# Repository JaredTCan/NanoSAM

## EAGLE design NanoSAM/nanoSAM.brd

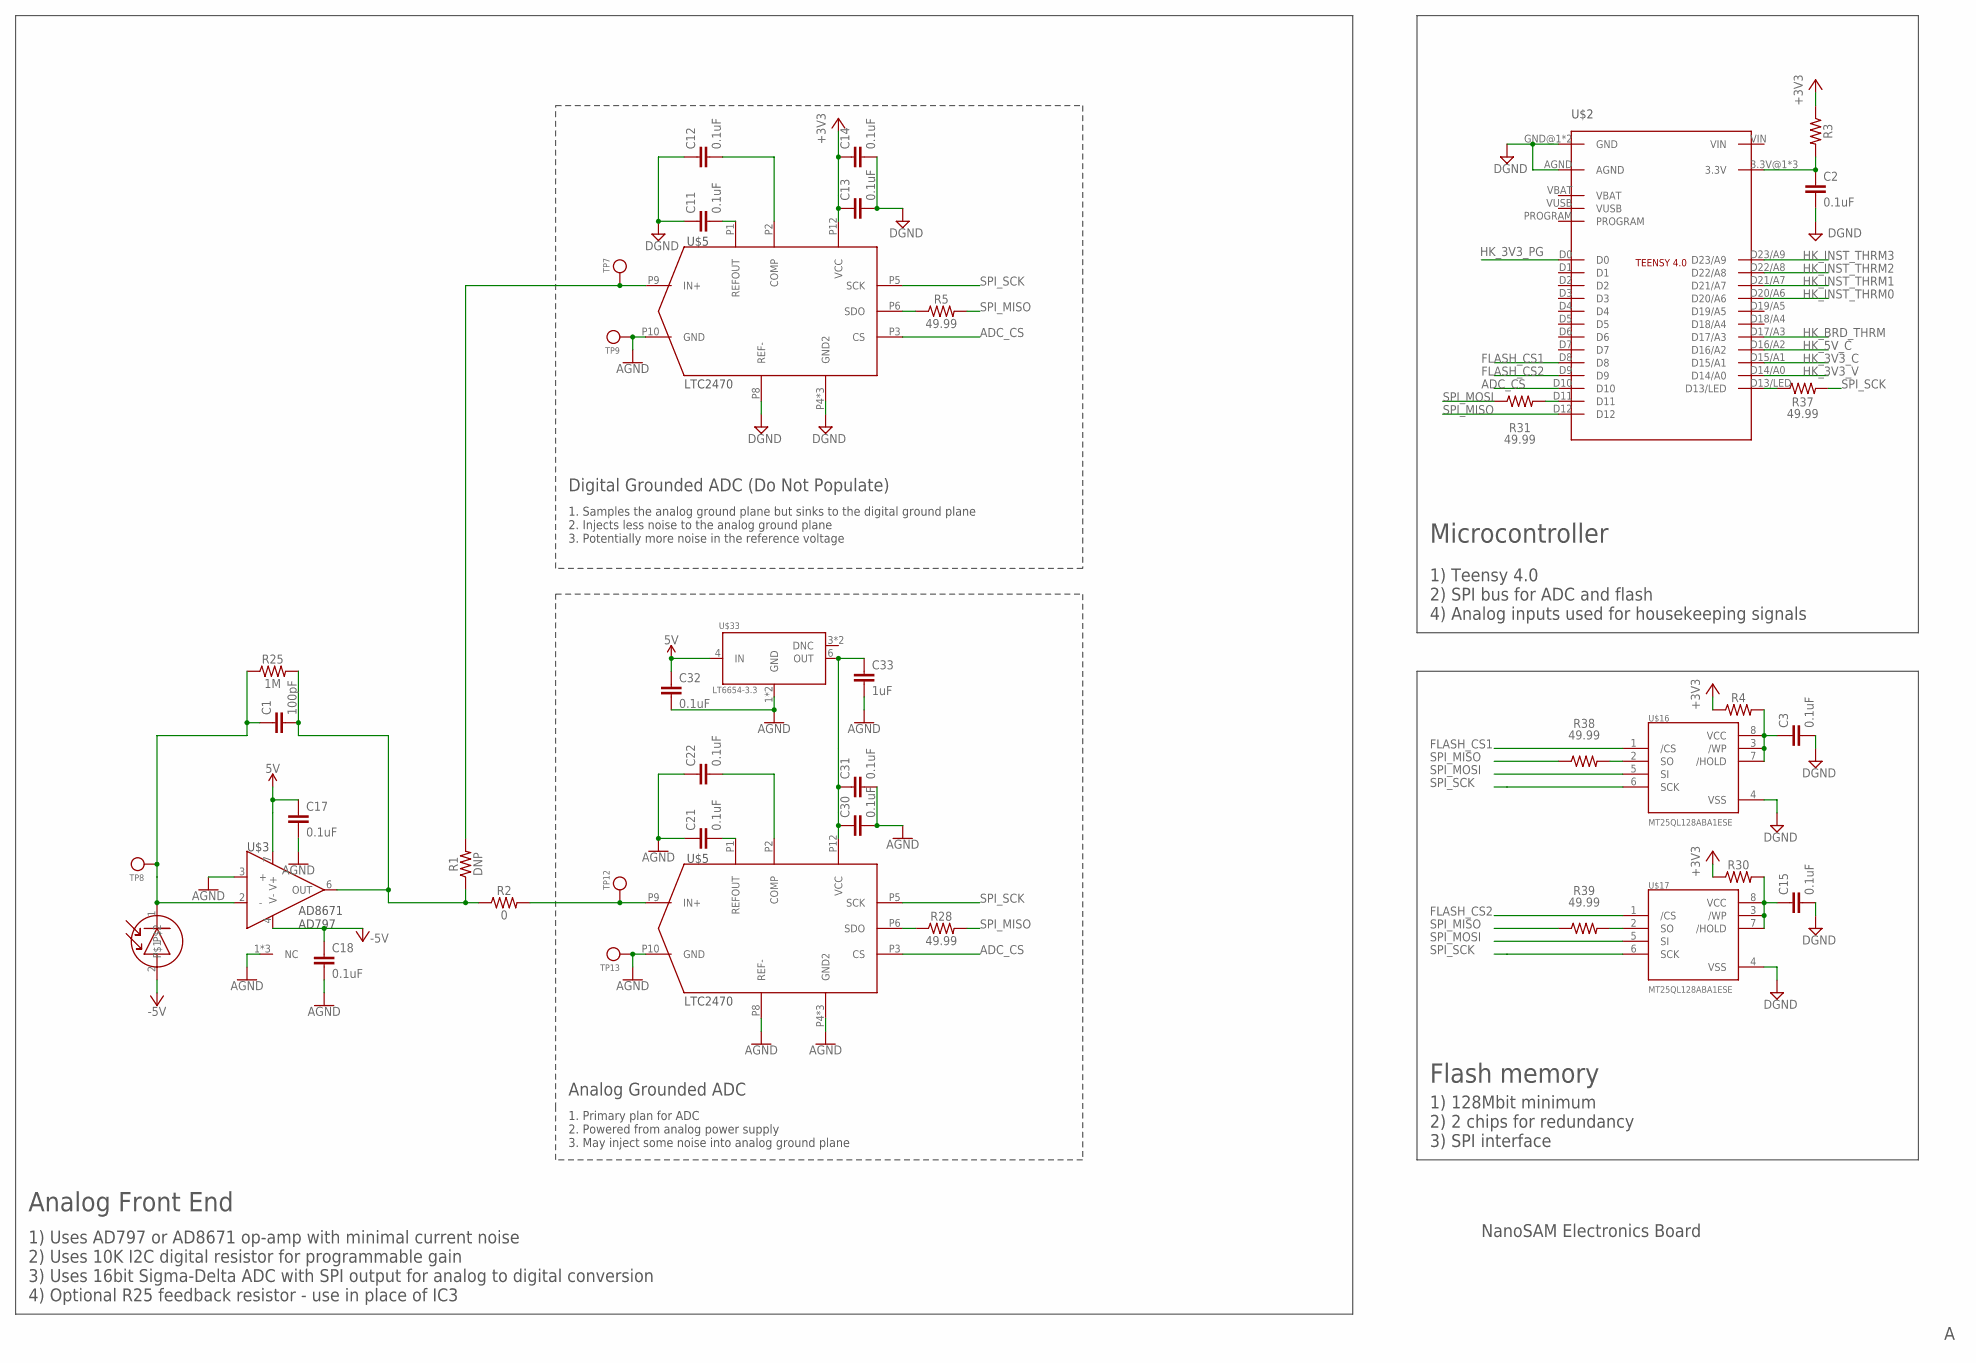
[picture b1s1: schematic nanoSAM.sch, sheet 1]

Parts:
C1: 100pF; 0603
C2, C3, C11, C12, C13, C14, C15, C17, C18, C21, C22, C30, C31, C32: 0.1uF; 0603
C33: 1uF; 0603
R1: DNP; 0805
R2: 0; 0805
R3, R4, R30: 0805
R5, R28, R31, R37, R38, R39: 49.99; 0805
R25: 1M; 0805
TP7, TP8, TP9, TP12, TP13: TESTPOINT; 1X01
U$1: PHOTODIODESYMBOLPD_CONN; 1X02
U$2: TEENSY4.0
U$3: AD8671; SO8
U$5, U$26: LTC2470; MSOP12
U$16, U$17: MT25QL128ABA1ESE; SO-08M
U$33: LT6654-3.3; SOT23-6L

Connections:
5V: C17.1, C32.1, U$3.7 (V+), U$33.4 (IN); also elsewhere on the board
+3V3: C13.1, C14.1, R3.1, R4.1, R30.1, U$5.P12 (VCC); also elsewhere on the board
-5V: C18.1, U$1.2, U$3.4 (V-); also elsewhere on the board
ADC_CS: U$2.D10, U$5.P3 (CS), U$26.P3 (CS)
AGND: C17.2, C18.2, C21.1, C22.1, C30.2, C31.2, C32.2, C33.2, TP9.1, TP13.1, U$3.1 (NC), U$3.3 (+), U$3.5 (NC), U$3.8 (NC), U$5.P10 (GND), U$26.P4 (GND2), U$26.P7 (GND2), U$26.P8 (REF-), U$26.P10 (GND), U$26.P11 (GND2), U$33.1 (GND), U$33.2 (GND); also elsewhere on the board
DGND: C2.2, C3.2, C11.1, C12.1, C13.2, C14.2, C15.2, U$2.AGND, U$2.GND@1 (GND), U$2.GND@2 (GND), U$5.P4 (GND2), U$5.P7 (GND2), U$5.P8 (REF-), U$5.P11 (GND2), U$16.4 (VSS), U$17.4 (VSS); also elsewhere on the board
FLASH_CS1: U$2.D8, U$16.1 (/CS)
FLASH_CS2: U$2.D9, U$17.1 (/CS)
HK_3V3_C: U$2.D15/A1; also elsewhere on the board
HK_3V3_PG: U$2.D0; also elsewhere on the board
HK_3V3_V: U$2.D14/A0; also elsewhere on the board
HK_5V_C: U$2.D16/A2; also elsewhere on the board
HK_BRD_THRM: U$2.D17/A3; also elsewhere on the board
HK_INST_THRM0: U$2.D20/A6; also elsewhere on the board
HK_INST_THRM1: U$2.D21/A7; also elsewhere on the board
HK_INST_THRM2: U$2.D22/A8; also elsewhere on the board
HK_INST_THRM3: U$2.D23/A9; also elsewhere on the board
unnamed: C1.1, R25.1, TP8.1, U$1.1, U$3.2 (-)
unnamed: C1.2, R1.1, R2.1, R25.2, U$3.6 (OUT)
unnamed: R1.2, TP7.1, U$5.P9 (IN+)
unnamed: C2.1, R3.2, U$2.3.3V@1 (3.3V), U$2.3.3V@2 (3.3V), U$2.ON/OFF (3.3V)
unnamed: R2.2, TP12.1, U$26.P9 (IN+)
unnamed: C3.1, R4.2, U$16.3 (/WP), U$16.7 (/HOLD), U$16.8 (VCC)
unnamed: C22.2, U$26.P2 (COMP)
unnamed: C12.2, U$5.P2 (COMP)
unnamed: C11.2, U$5.P1 (REFOUT)
unnamed: C21.2, U$26.P1 (REFOUT)
unnamed: C30.1, C31.1, C33.1, U$26.P12 (VCC), U$33.6 (OUT)
unnamed: C15.1, R30.2, U$17.3 (/WP), U$17.7 (/HOLD), U$17.8 (VCC)
unnamed: R5.1, U$5.P6 (SDO)
unnamed: R28.1, U$26.P6 (SDO)
unnamed: R31.2, U$2.D11
unnamed: R37.1, U$2.D13/LED
unnamed: R38.2, U$16.2 (SO)
unnamed: R39.2, U$17.2 (SO)
SPI_MISO: R5.2, R28.2, R38.1, R39.1, U$2.D12
SPI_MOSI: R31.1, U$16.5 (SI), U$17.5 (SI)
SPI_SCK: R37.2, U$5.P5 (SCK), U$16.6 (SCK), U$17.6 (SCK), U$26.P5 (SCK)

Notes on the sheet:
Analog Front End
Microcontroller
Flash memory
1) Uses AD797 or AD8671 op-amp with minimal current noise 2) Uses 10K I2C digital resistor for programmable gain 3) Uses 16bit Sigma-Delta ADC with SPI output for analog to digital conversion 4) Optional R25 feedback resistor - use in place of IC3
1) Teensy 4.0 2) SPI bus for ADC and flash 4) Analog inputs used for housekeeping signals
1) 128Mbit minimum 2) 2 chips for redundancy 3) SPI interface
AD8671 AD797
U$3
U$2
LTC2470
U$5
NanoSAM Electronics Board
Analog Grounded ADC
1. Primary plan for ADC 2. Powered from analog power supply 3. May inject some noise into analog ground plane
Digital Grounded ADC (Do Not Populate)
1. Samples the analog ground plane but sinks to the digital ground plane 2. Injects less noise to the analog ground plane 3. Potentially more noise in the reference voltage

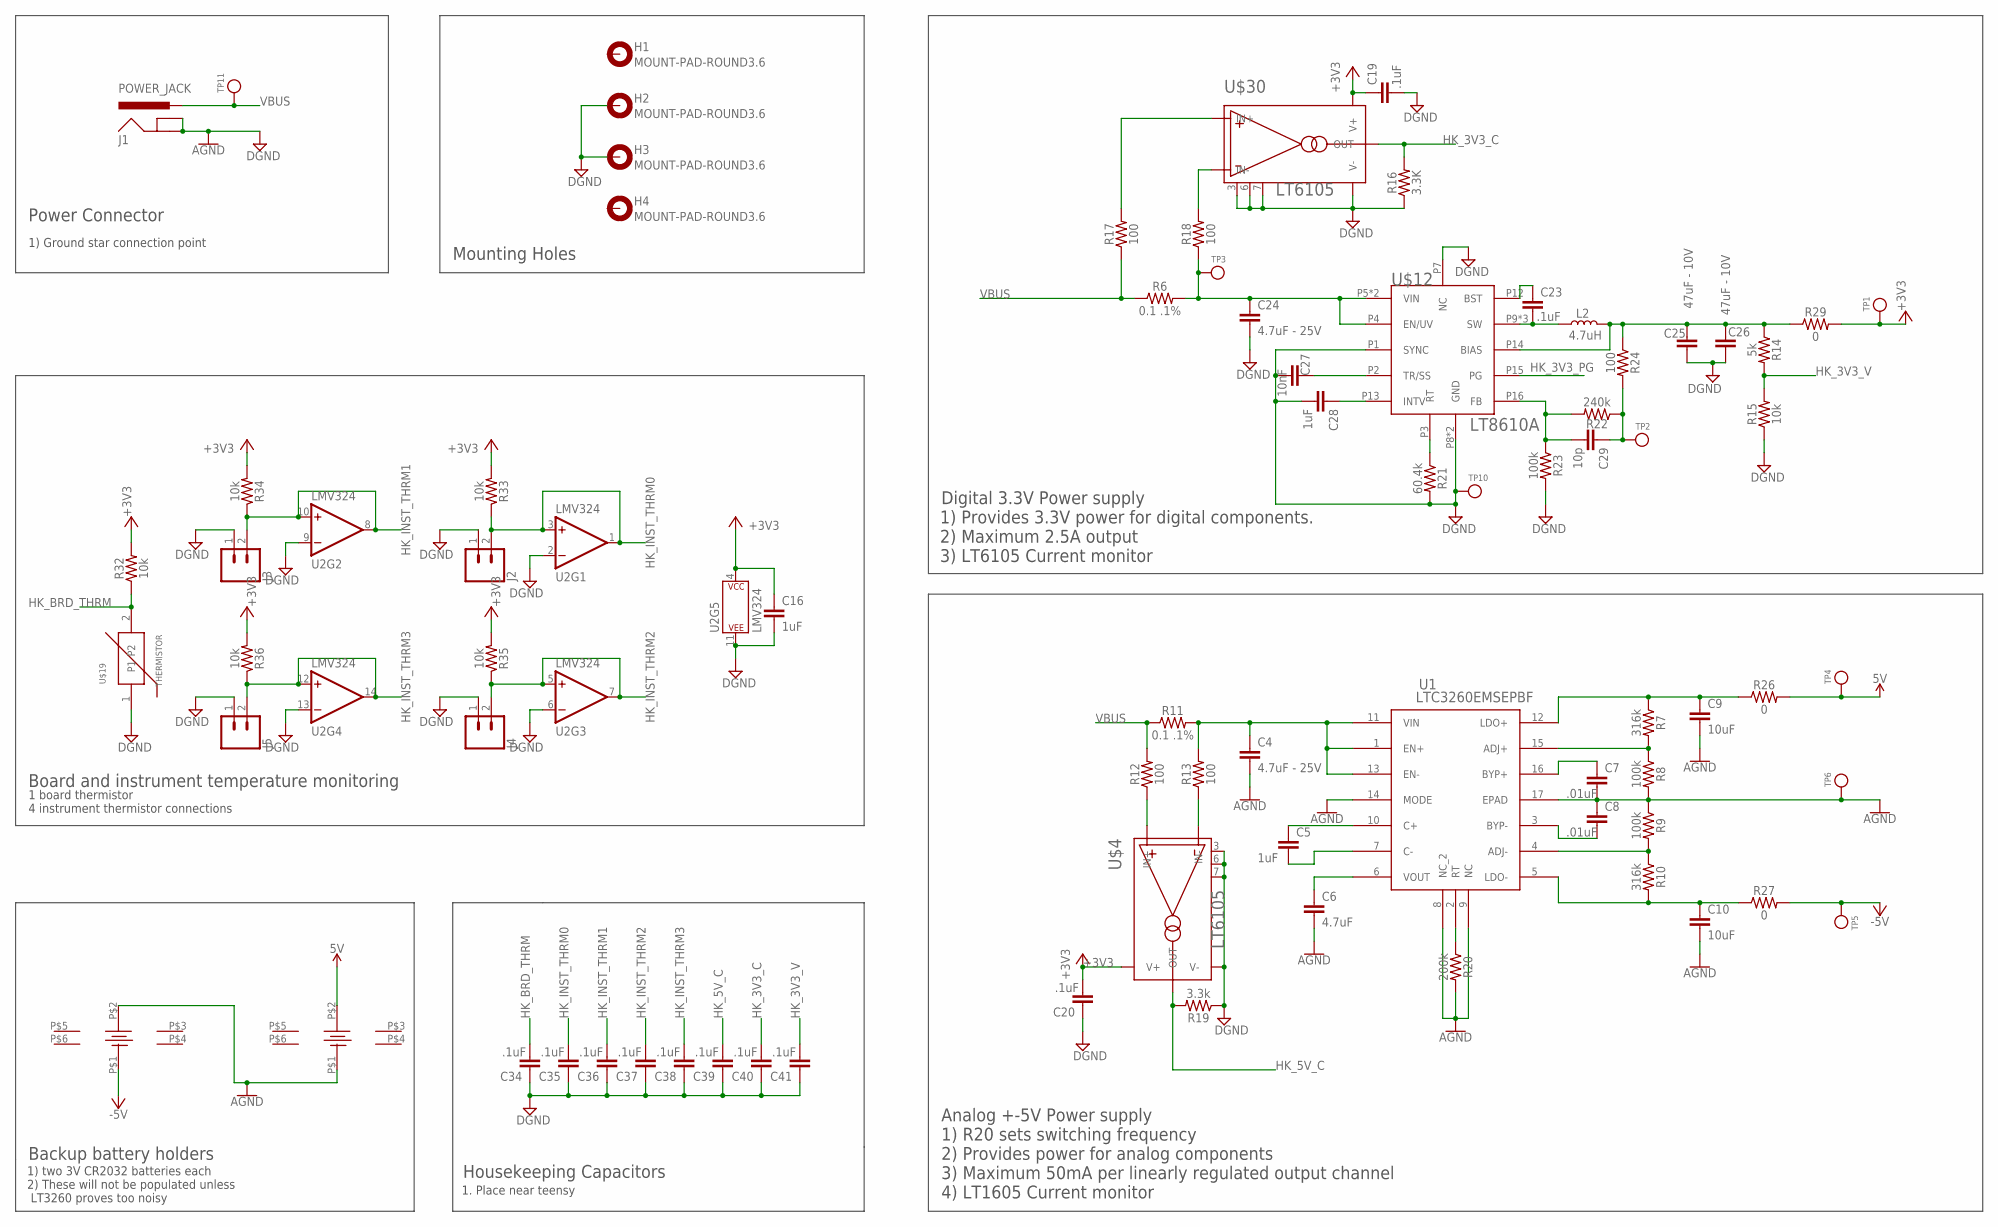
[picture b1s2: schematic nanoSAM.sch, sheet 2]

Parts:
C4, C24: 4.7uF - 25V; 1206
C5: 1uF; 1206
C6: 4.7uF; 1206
C7, C8: .01uF; 1206
C9, C10: 10uF; 1206
C16, C28: 1uF; 0603
C19, C20, C23, C34, C35, C36, C37, C38, C39, C40, C41: .1uF; 0603
C25, C26: 47uF - 10V; 1210
C27: 10nF; 0603
C29: 10p; 0603
H1, H2, H3, H4: MOUNT-PAD-ROUND3.6; 3,6-PAD
J1: POWER_JACK; POWER_JACK_PTH
J2, J3, J4, J5: CONN_02; 1X02
L2: 4.7uH; WE-HCI
R6, R11: 0.1 .1%; 1206
R7, R10: 316k; 0603
R8, R9, R23: 100k; 0603
R12, R13, R17, R18, R24: 100; 0603
R14: 5k; 0603
R15: 10k; 0603
R16: 3.3K; 0603
R19: 3.3k; 0603
R20: 200k; 0603
R21: 60.4k; 0603
R22: 240k; 0603
R26, R27: 0; 0603
R29: 0; 1206
R32, R33, R34, R35, R36: 10k; 1206
TP1, TP2, TP3, TP4, TP5, TP6, TP10, TP11: TESTPOINT; 1X01
U1: LTC3260EMSEPBF; MSOP-16_MSE
U2: LMV324; SO14
U$4, U$30: LT6105; MSOP8
U$12: LT8610A; MSOP16
U$19: THERMISTOR; M0805
U$20, U$21: CR2032

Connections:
5V: R26.2, TP4.1, U$21.P$2; also elsewhere on the board
+3V3: C16.1, C19.1, C20.2, R29.2, R32.2, R33.2, R34.2, R35.2, R36.2, TP1.1, U2.4 (P$V+), U$4.2 (V+), U$30.2 (V+); also elsewhere on the board
-5V: R27.2, TP5.1, U$20.P$1; also elsewhere on the board
AGND: C4.2, C6.2, C7.2, C8.1, C9.2, C10.2, R8.2, R9.1, R20.2, TP6.1, U1.8 (NC_2), U1.9 (NC), U1.14 (MODE), U1.17 (EPAD), U$20.P$2, U$21.P$1; also elsewhere on the board
DGND: C16.2, C19.2, C20.1, C24.2, C25.2, C26.2, C27.2, C28.2, C34.1, C35.1, C36.1, C37.1, C38.1, C39.1, C40.1, C41.1, H2.B3,6, H3.B3,6, J1.GND, J1.GNDBREAK, J2.1, J3.1, J4.1, J5.1, R15.1, R16.1, R19.1, R21.2, R23.2, TP10.1, U2.2 (-IN), U2.6 (-IN), U2.9 (-IN), U2.11 (P$V-), U2.13 (-IN), U$4.3, U$4.4 (V-), U$4.6, U$4.7, U$12.P1 (SYNC), U$12.P7 (NC), U$12.P8 (GND), U$12.P17 (GND), U$19.1, U$30.3, U$30.4 (V-), U$30.6, U$30.7; also elsewhere on the board
HK_3V3_C: C40.2, R16.2, U$30.5 (OUT); also elsewhere on the board
HK_3V3_PG: U$12.P15 (PG); also elsewhere on the board
HK_3V3_V: C41.2, R14.2, R15.2; also elsewhere on the board
HK_5V_C: C39.2, R19.2, U$4.5 (OUT); also elsewhere on the board
HK_BRD_THRM: C34.2, R32.1, U$19.2; also elsewhere on the board
HK_INST_THRM0: C35.2, J2.2, R33.1, U2.1 (OUT), U2.3 (+IN); also elsewhere on the board
HK_INST_THRM1: C36.2, J3.2, R34.1, U2.8 (OUT), U2.10 (+IN); also elsewhere on the board
HK_INST_THRM2: C37.2, J4.2, R35.1, U2.5 (+IN), U2.7 (OUT); also elsewhere on the board
HK_INST_THRM3: C38.2, J5.2, R36.1, U2.12 (+IN), U2.14 (OUT); also elsewhere on the board
unnamed: C7.1, U1.16 (BYP+)
unnamed: R7.2, R8.1, U1.15 (ADJ+)
unnamed: C6.1, U1.6 (VOUT)
unnamed: R17.2, U$30.8 (IN+)
unnamed: R9.2, R10.1, U1.4 (ADJ-)
unnamed: R18.2, U$30.1 (IN-)
unnamed: C8.2, U1.3 (BYP-)
unnamed: C4.1, R11.2, R13.2, U1.1 (EN+), U1.11 (VIN), U1.13 (EN-)
unnamed: R12.1, U$4.8 (IN+)
unnamed: R13.1, U$4.1 (IN-)
unnamed: C5.1, U1.10 (C+)
unnamed: C5.2, U1.7 (C-)
unnamed: C9.1, R7.1, R26.1, U1.12 (LDO+)
unnamed: R20.1, U1.2 (RT)
unnamed: C10.1, R10.2, R27.1, U1.5 (LDO-)
unnamed: C28.1, U$12.P13 (INTV)
unnamed: C25.1, C26.1, L2.P$2 (2), R14.1, R24.1, R29.1, U$12.P14 (BIAS)
unnamed: C27.1, U$12.P2 (TR/SS)
unnamed: R21.1, U$12.P3 (RT)
unnamed: C23.1, U$12.P12 (BST)
unnamed: C23.2, L2.P$1 (1), U$12.P9 (SW), U$12.P10 (SW), U$12.P11 (SW)
unnamed: C29.2, R22.2, R23.1, U$12.P16 (FB)
unnamed: C29.1, R22.1, R24.2, TP2.1
unnamed: C24.1, R6.2, R18.1, TP3.1, U$12.P4 (EN/UV), U$12.P5 (VIN), U$12.P6 (VIN)
VBUS: J1.PWR, R6.1, R11.1, R12.2, R17.1, TP11.1

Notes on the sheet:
Digital 3.3V Power supply
Analog +-5V Power supply
Power Connector
1) Ground star connection point
Mounting Holes
1) R20 sets switching frequency 2) Provides power for analog components 3) Maximum 50mA per linearly regulated output channel 4) LT1605 Current monitor
1) Provides 3.3V power for digital components. 2) Maximum 2.5A output 3) LT6105 Current monitor
Board and instrument temperature monitoring
1 board thermistor 4 instrument thermistor connections
Backup battery holders
1) two 3V CR2032 batteries each 2) These will not be populated unless LT3260 proves too noisy
Housekeeping Capacitors
1. Place near teensy

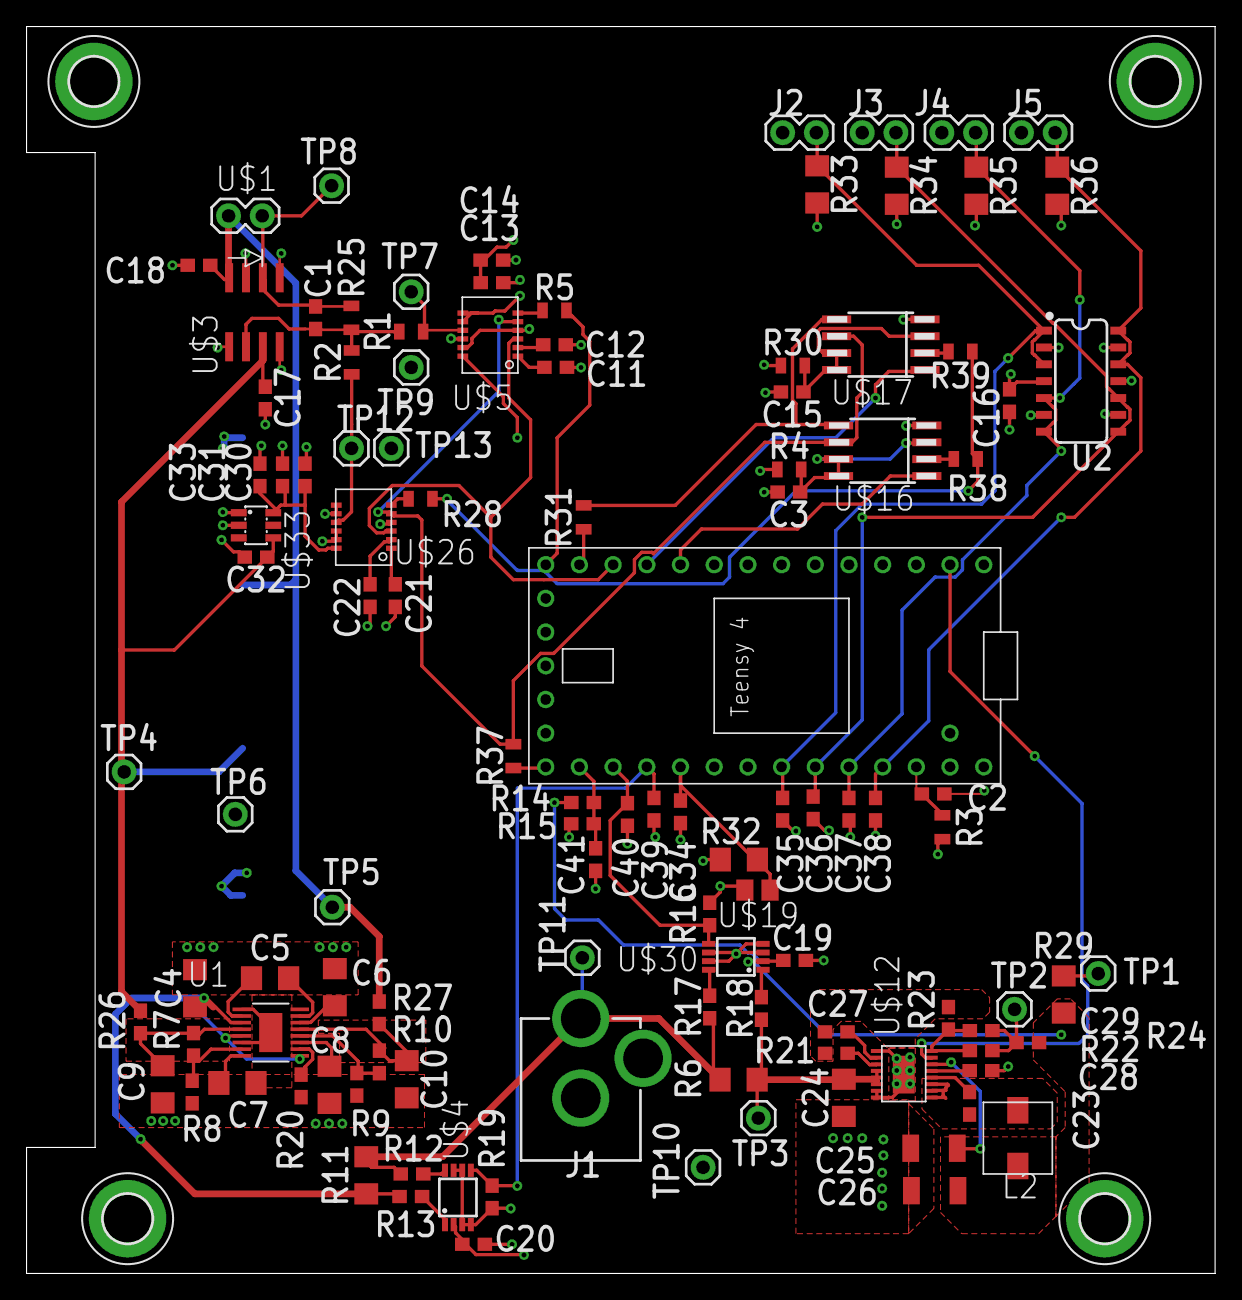
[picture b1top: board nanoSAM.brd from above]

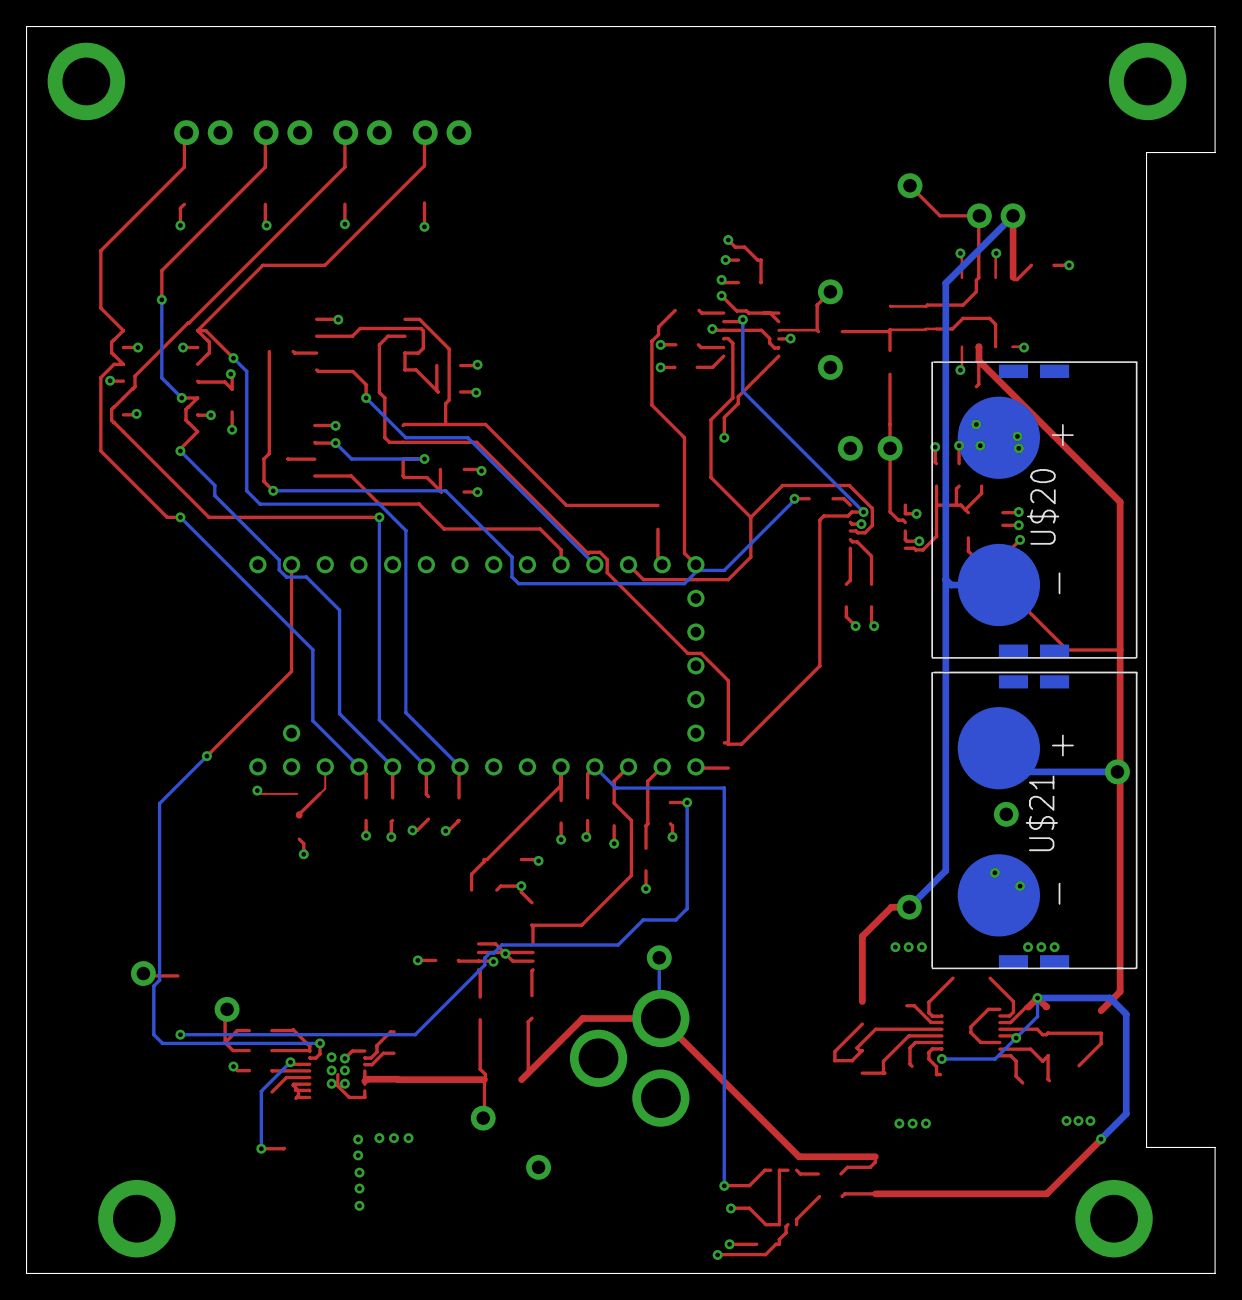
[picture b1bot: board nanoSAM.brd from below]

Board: 4 copper layers, 89.6 x 94.0 mm, 119 parts (2 on the bottom side), 63 nets.

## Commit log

2019-10-27 starting repo
2019-10-27 added schematic
2019-10-27 added libraries
2019-10-27 added AD8671 library
2019-10-27 updated schematic
2019-10-27 Added ADC library part
2019-10-27 updated sch
2019-10-27 added library
2019-10-27 removed test
2019-10-28 added teensy 4.0 library
2019-10-28 added teensy library successfully
2019-11-09 Split analog and digital grounds
2019-11-09 Updated teensy to 4.0, added analog housekeeping signals to teensy
2019-11-09 Added flash chips
2019-11-09 added mounting holes
2019-11-09 added testpoints
2019-11-09 added schematic pdf
2019-11-12 added thermistors for temp monitoring and changed current monitoring circuit
2019-11-12 updated pdf
2019-11-13 added more thermistor connections
2019-11-14 started layout
2019-11-15 routed analog signals, added R3 and C2 by microcontroller
2019-11-15 added power plane
2019-11-15 Added R4, R30, C15, C14 to flash.
2019-11-15 moved some resistors around
2019-11-15 Edited Bipolar power supply
2019-11-17 routed +3v3 power supply
2019-11-17 Finished part placements and bus wiring
2019-11-17 fixed some DRC errors
2019-11-18 Fixed labels and started to add coin cell battery backup
2019-11-20 Added Coin Cell Battery library, schematic, and board.
2019-11-21 added some documentation to schematic, added datasheets folder
2019-11-25 added unity gain op-amp buffer for instrument housekeeping
2019-11-27 Added SNR Calculations
2019-11-30 updated dark noise calculation
2019-12-01 added some stuff, fixed some stuff
2019-12-02 added a bit to SNR calc
2019-12-14 updated some stuff
2019-12-14 added options for grounding ADCs
2019-12-14 Added library for LT6654
2019-12-14 Added analog grounded ADC power regulator
2019-12-14 Finished fixing stuff
2019-12-14 changed a border for the A E S T H E T I C
2019-12-14 more A E S T H E T I C
2019-12-14 Added HK Capacitors
2019-12-15 added changes to PCB board layout including 3.3V linear regulator
2019-12-15 fixed some PCB issues
2020-01-12 Updated board dimensions to match stack plate
2020-01-15 updated some values
2020-01-15 added BOM
2020-01-24 added to software folder
2020-01-24 added manufacturing files
2020-01-24 added possible flash library
2020-01-27 Add files via upload
    Added new code and variables. Condition for data capture
2020-02-17 Updated main.cpp
    After Monday 2/17 meeting with Sara, Jared, and Jessica
2020-02-20 Main Code with libraries
2020-03-09 fixed footprint, broke other things
2020-03-12 updated PCB

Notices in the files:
parts and their libraries:
SparkFun-Capacitors: Licensing: Creative Commons ShareAlike 4.0 International - https://creativecommons.org/licenses/by-sa/4.0
